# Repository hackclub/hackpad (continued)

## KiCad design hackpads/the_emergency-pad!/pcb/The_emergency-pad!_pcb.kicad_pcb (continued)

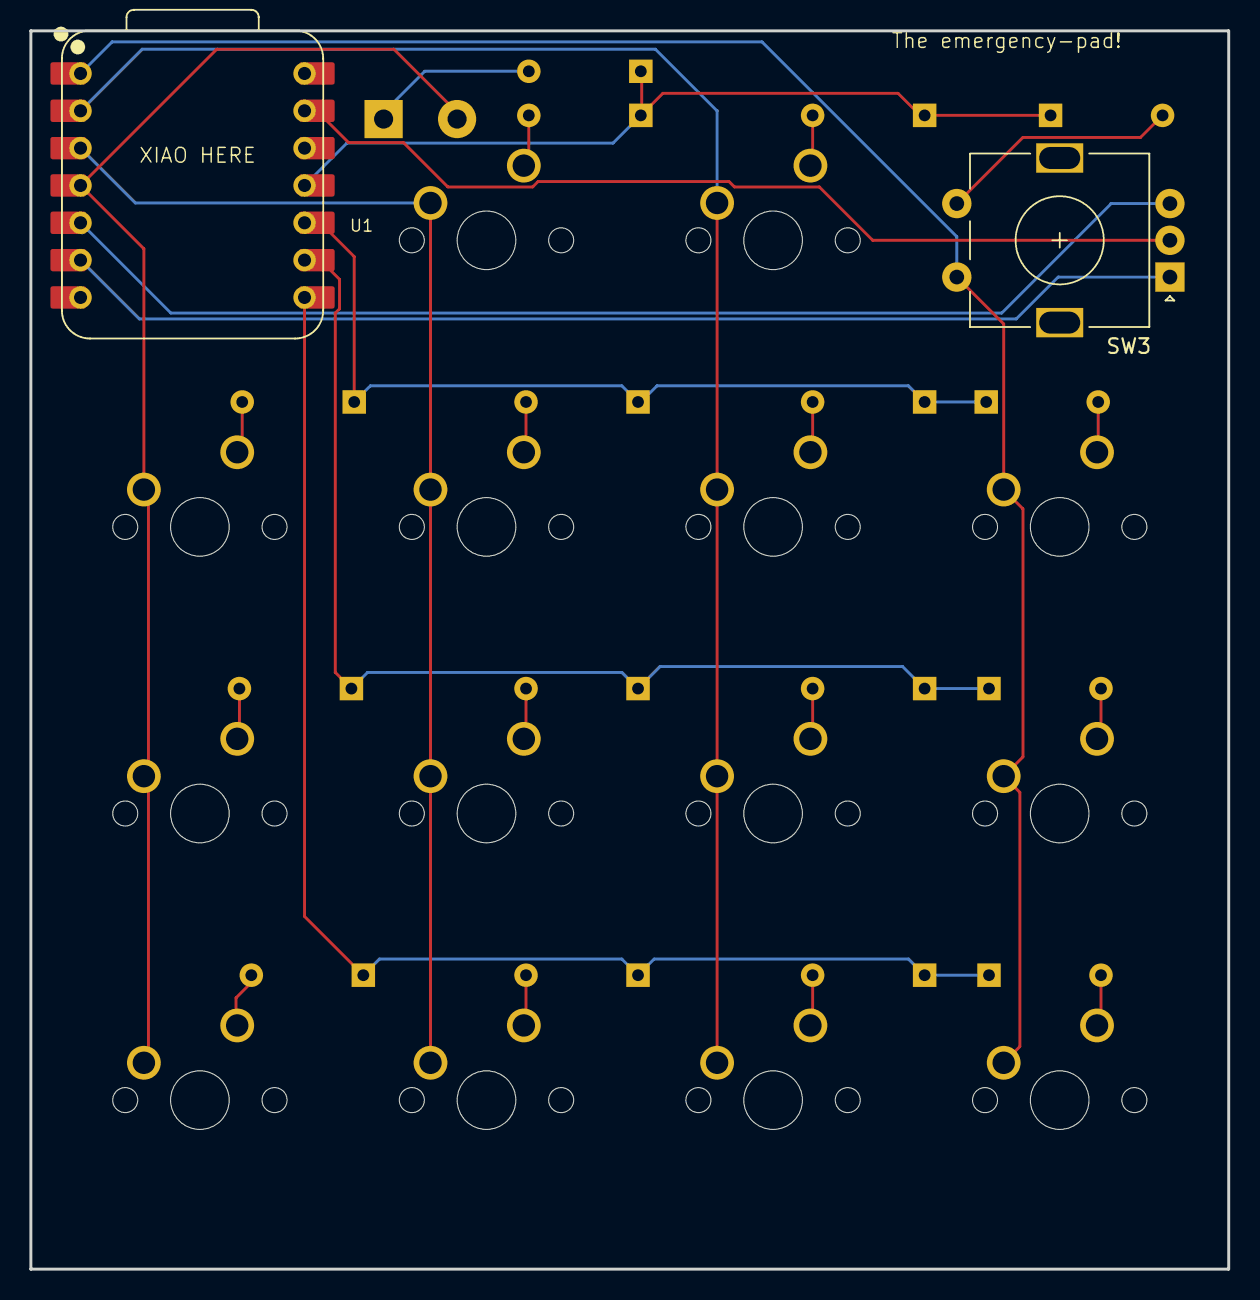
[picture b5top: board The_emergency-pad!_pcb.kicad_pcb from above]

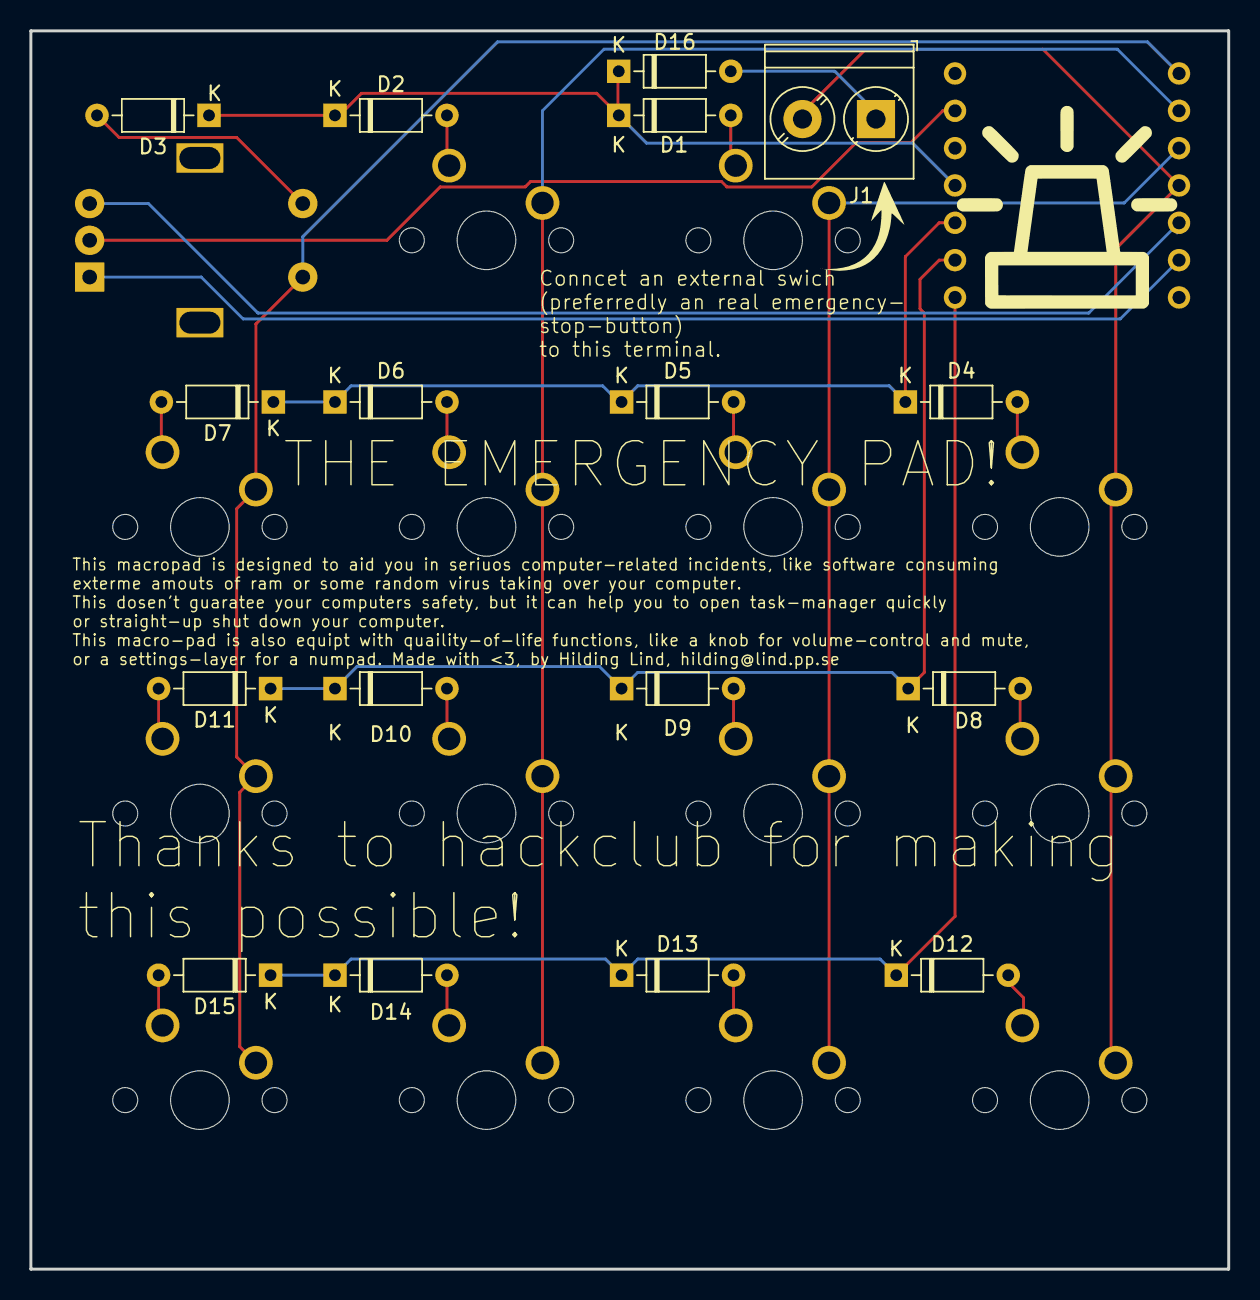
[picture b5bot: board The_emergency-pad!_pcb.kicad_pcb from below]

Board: 2 copper layers, 81.5 x 84.2 mm, 33 parts (17 on the bottom side), 27 nets.

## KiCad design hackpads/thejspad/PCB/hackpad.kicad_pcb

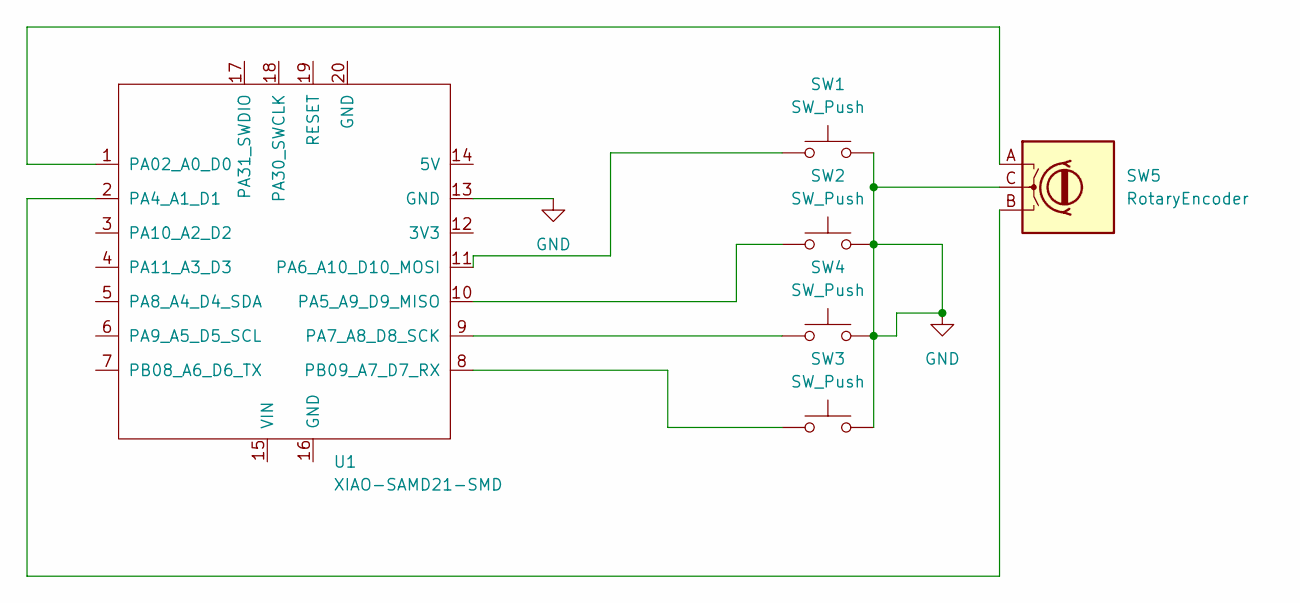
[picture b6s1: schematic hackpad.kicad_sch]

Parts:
SW1, SW2, SW3, SW4: SW_Push; SW_Cherry_MX_1.00u_PCB
SW5: RotaryEncoder; RotaryEncoder_Alps_EC11E_Vertical_H20mm_CircularMountingHol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
U1: XIAO-SAMD21-SMD; XIAO-RP2040-DIP

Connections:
GND: SW1.2, SW2.2, SW3.2, SW4.2, SW5.C, U1.13 (GND)
unnamed: SW5.A, U1.1 (PA02_A0_D0)
unnamed: SW5.B, U1.2 (PA4_A1_D1)
unnamed: SW2.1, U1.10 (PA5_A9_D9_MISO)
unnamed: SW1.1, U1.11 (PA6_A10_D10_MOSI)
unnamed: SW4.1, U1.9 (PA7_A8_D8_SCK)
unnamed: SW3.1, U1.8 (PB09_A7_D7_RX)

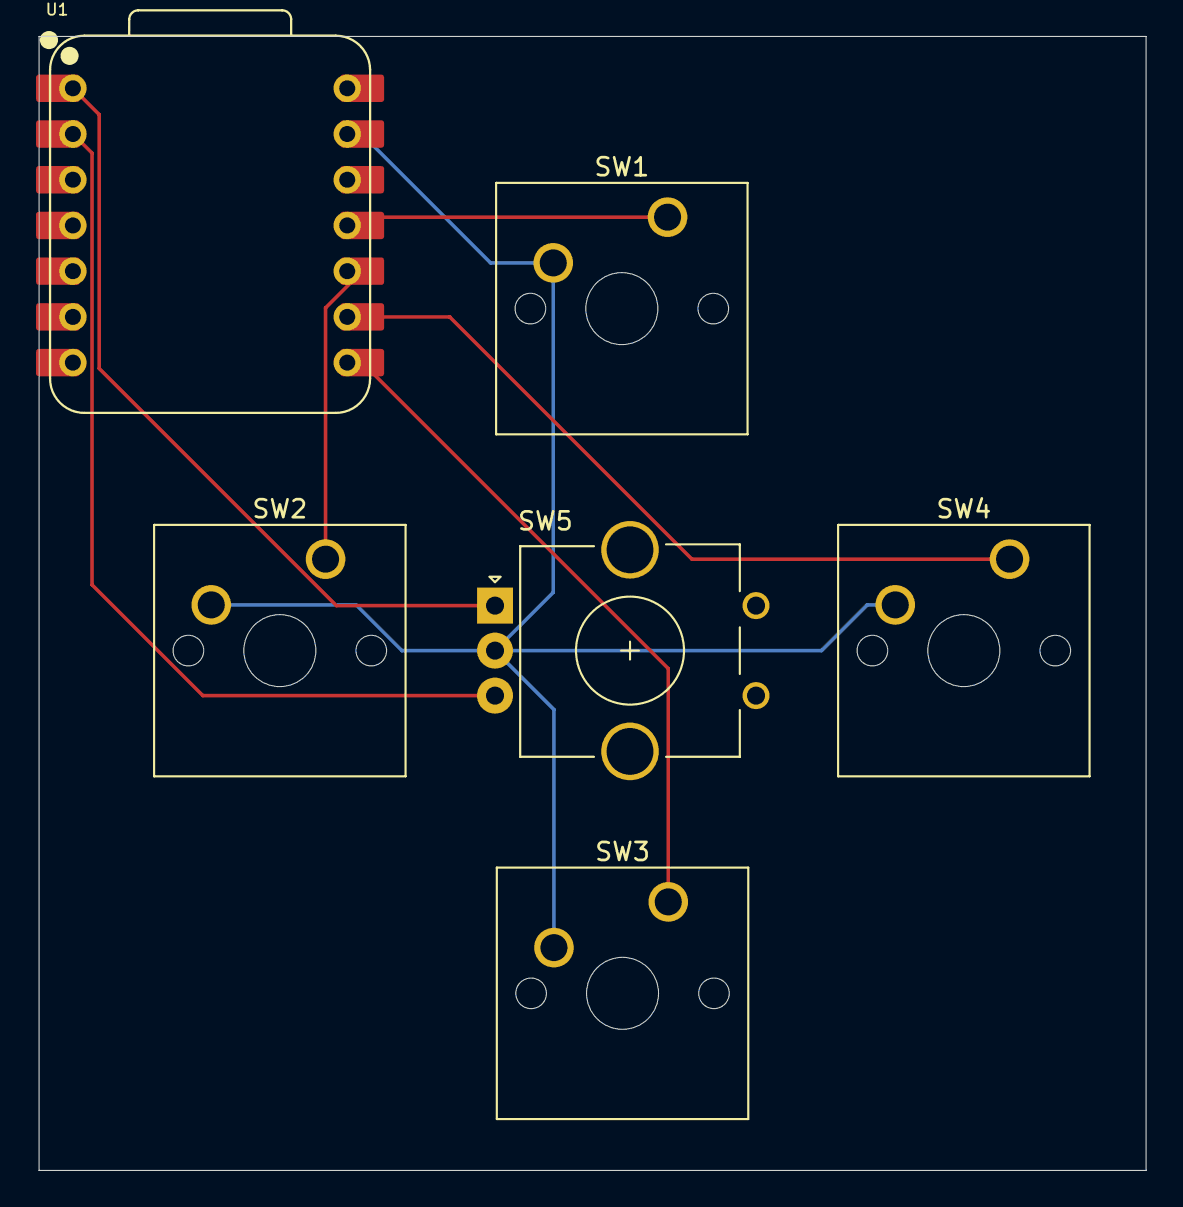
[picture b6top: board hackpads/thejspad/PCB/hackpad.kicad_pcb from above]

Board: 2 copper layers, 61.5 x 63.0 mm, 6 parts (0 on the bottom side), 7 nets.

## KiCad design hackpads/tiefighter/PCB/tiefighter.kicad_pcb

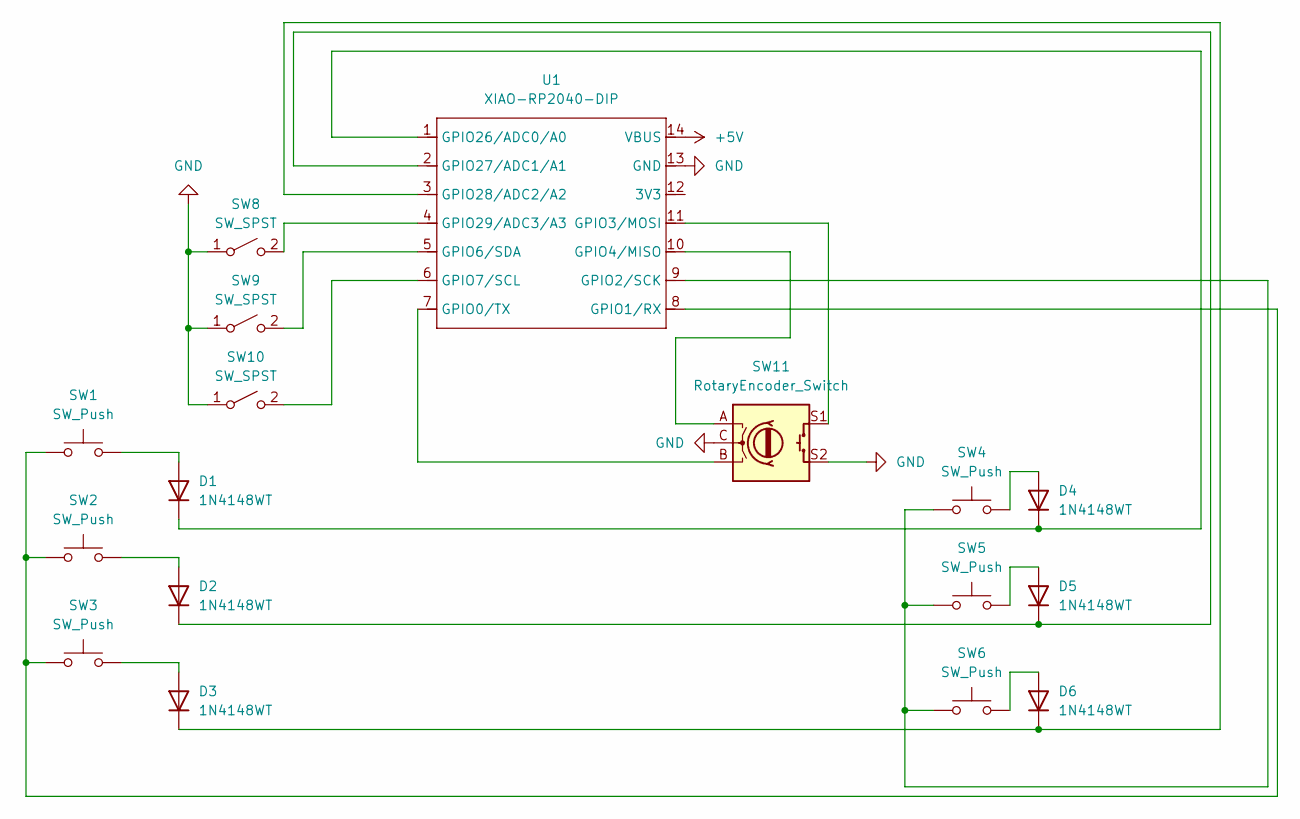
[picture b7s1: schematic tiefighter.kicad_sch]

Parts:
D1, D2, D3, D4, D5, D6: 1N4148WT; D_SOD-523
SW1, SW2, SW3, SW4, SW5, SW6: SW_Push; SW_Cherry_MX_1.00u_PCB
SW8, SW9, SW10: SW_SPST; ToggleSwitch_MTS-101_SPST
SW11: RotaryEncoder_Switch; RotaryEncoder_Alps_EC11E-Switch_Vertical_H20mm
U1: XIAO-RP2040-DIP

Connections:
+5V: U1.14 (VBUS)
GND: SW8.1 (A), SW9.1 (A), SW10.1 (A), SW11.C, SW11.S2, U1.13 (GND)
unnamed: D1.2 (A), SW1.2
unnamed: D1.1 (K), D4.1 (K), U1.1 (GPIO26/ADC0/A0)
unnamed: D2.2 (A), SW2.2
unnamed: D2.1 (K), D5.1 (K), U1.2 (GPIO27/ADC1/A1)
unnamed: D3.2 (A), SW3.2
unnamed: D3.1 (K), D6.1 (K), U1.3 (GPIO28/ADC2/A2)
unnamed: D4.2 (A), SW4.2
unnamed: D5.2 (A), SW5.2
unnamed: D6.2 (A), SW6.2
unnamed: SW8.2 (B), U1.4 (GPIO29/ADC3/A3)
unnamed: SW9.2 (B), U1.5 (GPIO6/SDA)
unnamed: SW10.2 (B), U1.6 (GPIO7/SCL)
unnamed: SW11.B, U1.7 (GPIO0/TX)
unnamed: SW1.1, SW2.1, SW3.1, U1.8 (GPIO1/RX)
unnamed: SW4.1, SW5.1, SW6.1, U1.9 (GPIO2/SCK)
unnamed: SW11.S1, U1.11 (GPIO3/MOSI)
unnamed: SW11.A, U1.10 (GPIO4/MISO)

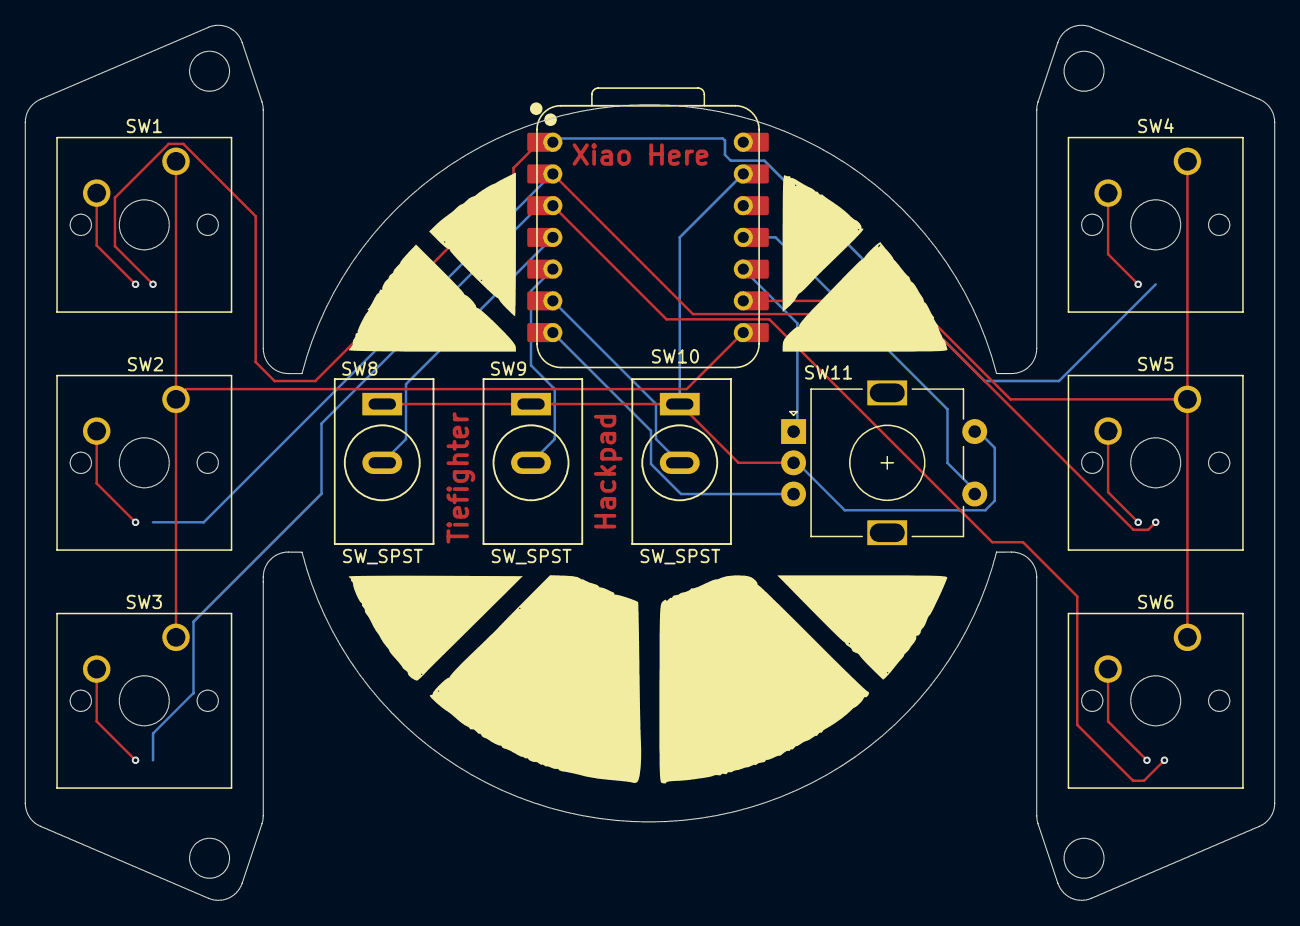
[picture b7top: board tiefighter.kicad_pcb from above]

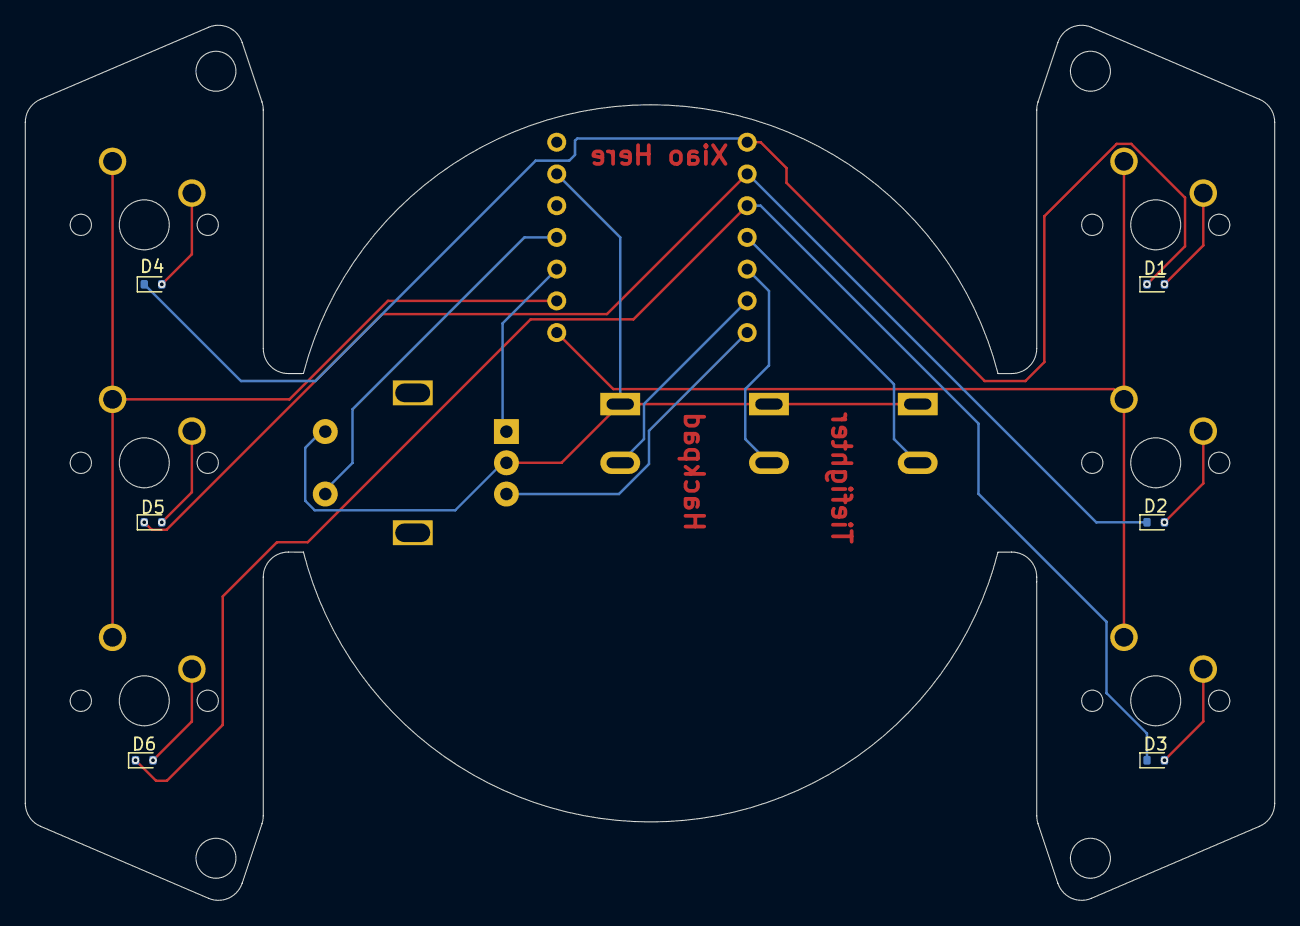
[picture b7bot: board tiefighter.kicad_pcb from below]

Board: 2 copper layers, 100.0 x 70.0 mm, 17 parts (6 on the bottom side), 18 nets.

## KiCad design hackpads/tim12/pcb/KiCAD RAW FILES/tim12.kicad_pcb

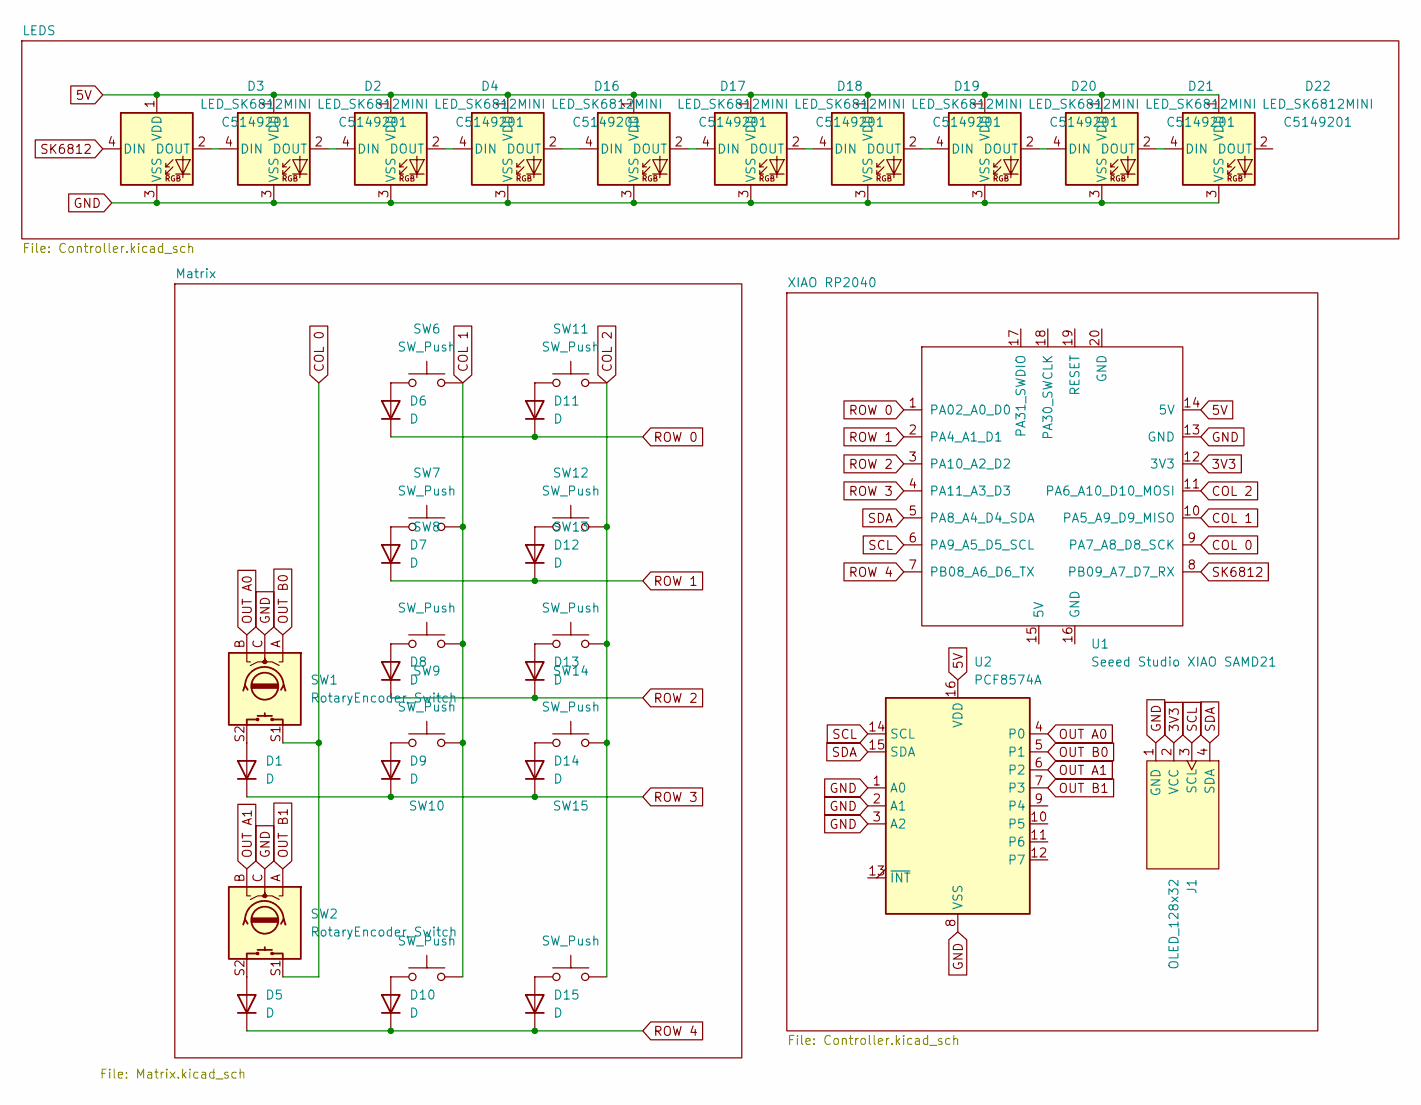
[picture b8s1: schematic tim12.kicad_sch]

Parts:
D1, D5, D6, D7, D8, D9, D10, D11, D12, D13, D14, D15: D; Diode_SOD-123
D2, D3, D4, D16, D17, D18, D19, D20, D21, D22: LED_SK6812MINI; LCSC C5149201
J1: OLED_128x32
SW1, SW2: RotaryEncoder_Switch; Encoder_EC11_MX
SW6, SW7, SW8, SW9, SW10, SW11, SW12, SW13, SW14, SW15: SW_Push; MX_Hotswap_1.00u
U1: Seeed Studio XIAO SAMD21; Seeed_XIAO_RP2040
U2: PCF8574A; N16

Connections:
3V3: J1.2 (VCC), U1.12 (3V3)
5V: D2.1 (VDD), D3.1 (VDD), D4.1 (VDD), D16.1 (VDD), D17.1 (VDD), D18.1 (VDD), D19.1 (VDD), D20.1 (VDD), D21.1 (VDD), D22.1 (VDD), U1.14 (5V), U2.16 (VDD)
COL 0: SW1.S1, SW2.S1, U1.9 (PA7_A8_D8_SCK)
COL 1: SW6.2, SW7.2, SW8.2, SW9.2, SW10.2, U1.10 (PA5_A9_D9_MISO)
COL 2: SW11.2, SW12.2, SW13.2, SW14.2, SW15.2, U1.11 (PA6_A10_D10_MOSI)
GND: D2.3 (VSS), D3.3 (VSS), D4.3 (VSS), D16.3 (VSS), D17.3 (VSS), D18.3 (VSS), D19.3 (VSS), D20.3 (VSS), D21.3 (VSS), D22.3 (VSS), J1.1 (GND), SW1.C, SW2.C, U1.13 (GND), U2.1 (A0), U2.2 (A1), U2.3 (A2), U2.8 (VSS)
unnamed: D1.2 (A), SW1.S2
unnamed: D2.4 (DIN), D3.2 (DOUT)
unnamed: D2.2 (DOUT), D4.4 (DIN)
unnamed: D5.2 (A), SW2.S2
unnamed: D6.2 (A), SW6.1
unnamed: D7.2 (A), SW7.1
unnamed: D8.2 (A), SW8.1
unnamed: D9.2 (A), SW9.1
unnamed: D10.2 (A), SW10.1
unnamed: D11.2 (A), SW11.1
unnamed: D12.2 (A), SW12.1
unnamed: D13.2 (A), SW13.1
unnamed: D14.2 (A), SW14.1
unnamed: D15.2 (A), SW15.1
unnamed: D4.2 (DOUT), D16.4 (DIN)
unnamed: D16.2 (DOUT), D17.4 (DIN)
unnamed: D17.2 (DOUT), D18.4 (DIN)
unnamed: D18.2 (DOUT), D19.4 (DIN)
unnamed: D19.2 (DOUT), D20.4 (DIN)
unnamed: D20.2 (DOUT), D21.4 (DIN)
unnamed: D21.2 (DOUT), D22.4 (DIN)
OUT A0: SW1.B, U2.4 (P0)
OUT A1: SW2.B, U2.6 (P2)
OUT B0: SW1.A, U2.5 (P1)
OUT B1: SW2.A, U2.7 (P3)
ROW 0: D6.1 (K), D11.1 (K), U1.1 (PA02_A0_D0)
ROW 1: D7.1 (K), D12.1 (K), U1.2 (PA4_A1_D1)
ROW 2: D8.1 (K), D13.1 (K), U1.3 (PA10_A2_D2)
ROW 3: D1.1 (K), D9.1 (K), D14.1 (K), U1.4 (PA11_A3_D3)
ROW 4: D5.1 (K), D10.1 (K), D15.1 (K), U1.7 (PB08_A6_D6_TX)
SCL: J1.3 (SCL), U1.6 (PA9_A5_D5_SCL), U2.14 (SCL)
SDA: J1.4 (SDA), U1.5 (PA8_A4_D4_SDA), U2.15 (SDA)
SK6812: D3.4 (DIN), U1.8 (PB09_A7_D7_RX)

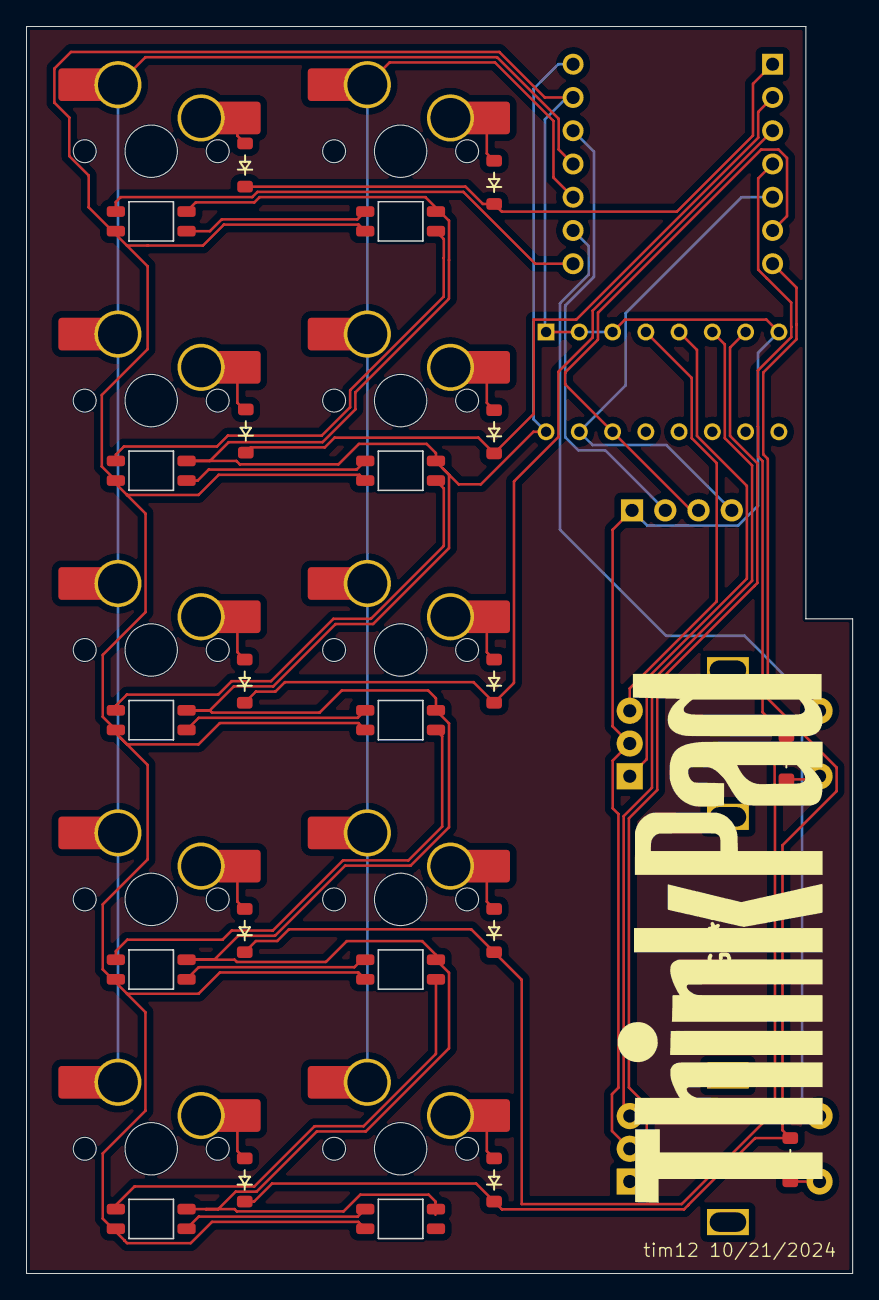
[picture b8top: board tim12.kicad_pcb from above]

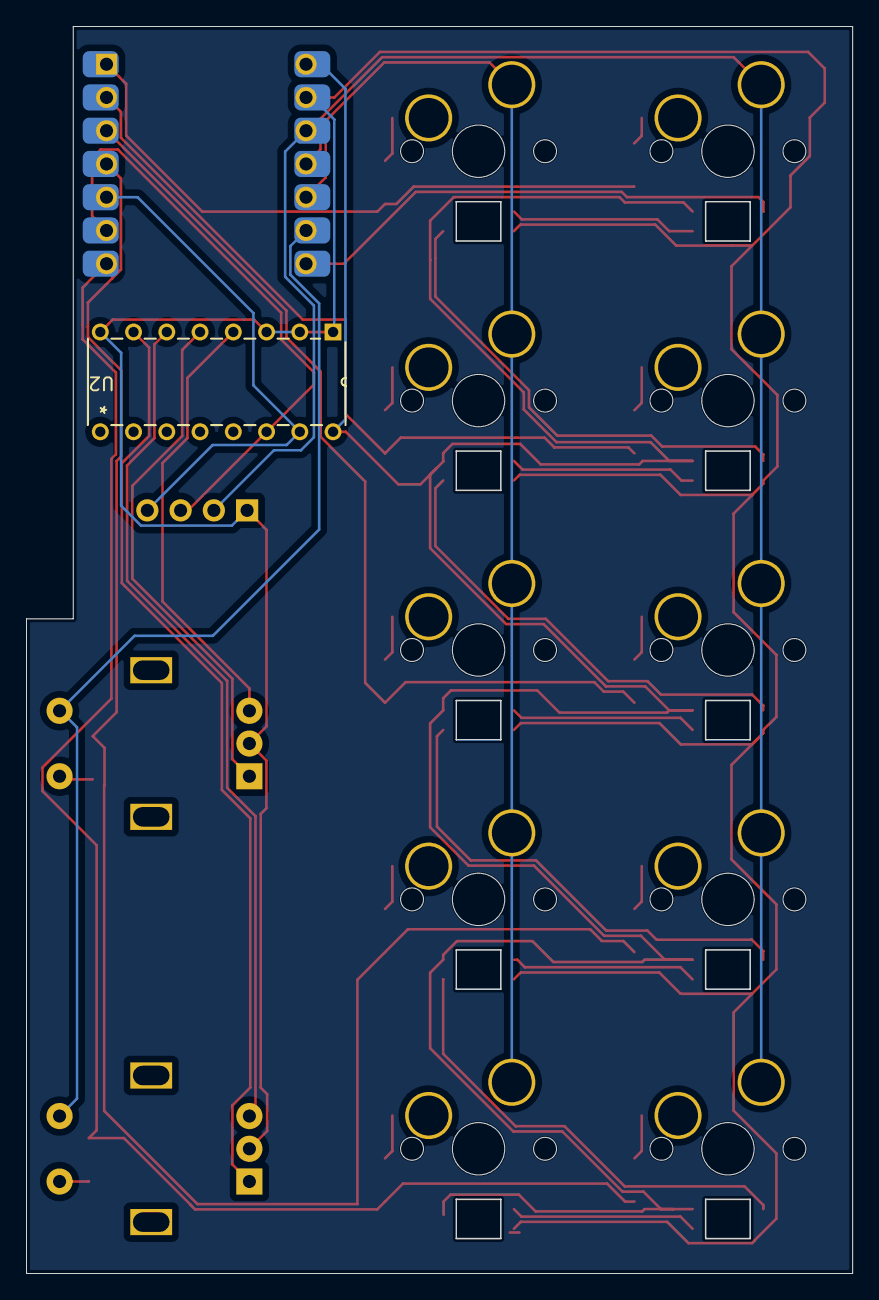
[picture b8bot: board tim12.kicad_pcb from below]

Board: 2 copper layers, 63.1 x 95.3 mm, 37 parts (5 on the bottom side), 39 nets.
